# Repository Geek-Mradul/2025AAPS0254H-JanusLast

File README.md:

# 🚀 Team JANUS Avionics - Round 3 PCB Design

This repository contains the PCB design solution for the final round of the Team JANUS Avionics Subsystem inductions for 2025-2026. The project involves creating a PCB layout from a provided schematic using KiCad.

---

## 📋 Task Requirements

The goal was to design a functional PCB based on a given schematic. The board includes an STM32 MCU, a BMP280 sensor, a USB-to-UART bridge, and a Micro-USB port for power and data.

The design adheres to the following key constraints as specified in the problem statement:
* **Component Footprints**: The problem statement allowed for modifying component footprints as required. For this design, standard footprints were used.
* **Trace Widths**: Separate trace widths are used for power and signal lines to ensure stable power delivery.
* **Ground Plane**: The bottom copper layer is dedicated to a solid ground plane for signal integrity and noise reduction.
* **Vias**: Vias are used as needed to route signals between the top and bottom layers.
* **Manual Routing**: All routing was performed manually; auto-routing was strictly prohibited.

---

## 📁 Repository Contents

* `NewFile.kicad_pro`: The main KiCad project file.
* `NewFile.kicad_sch`: The schematic file containing the complete circuit diagram.
* `NewFile.kicad_pcb`: The final PCB layout file.
* `README.md`: This file.

---

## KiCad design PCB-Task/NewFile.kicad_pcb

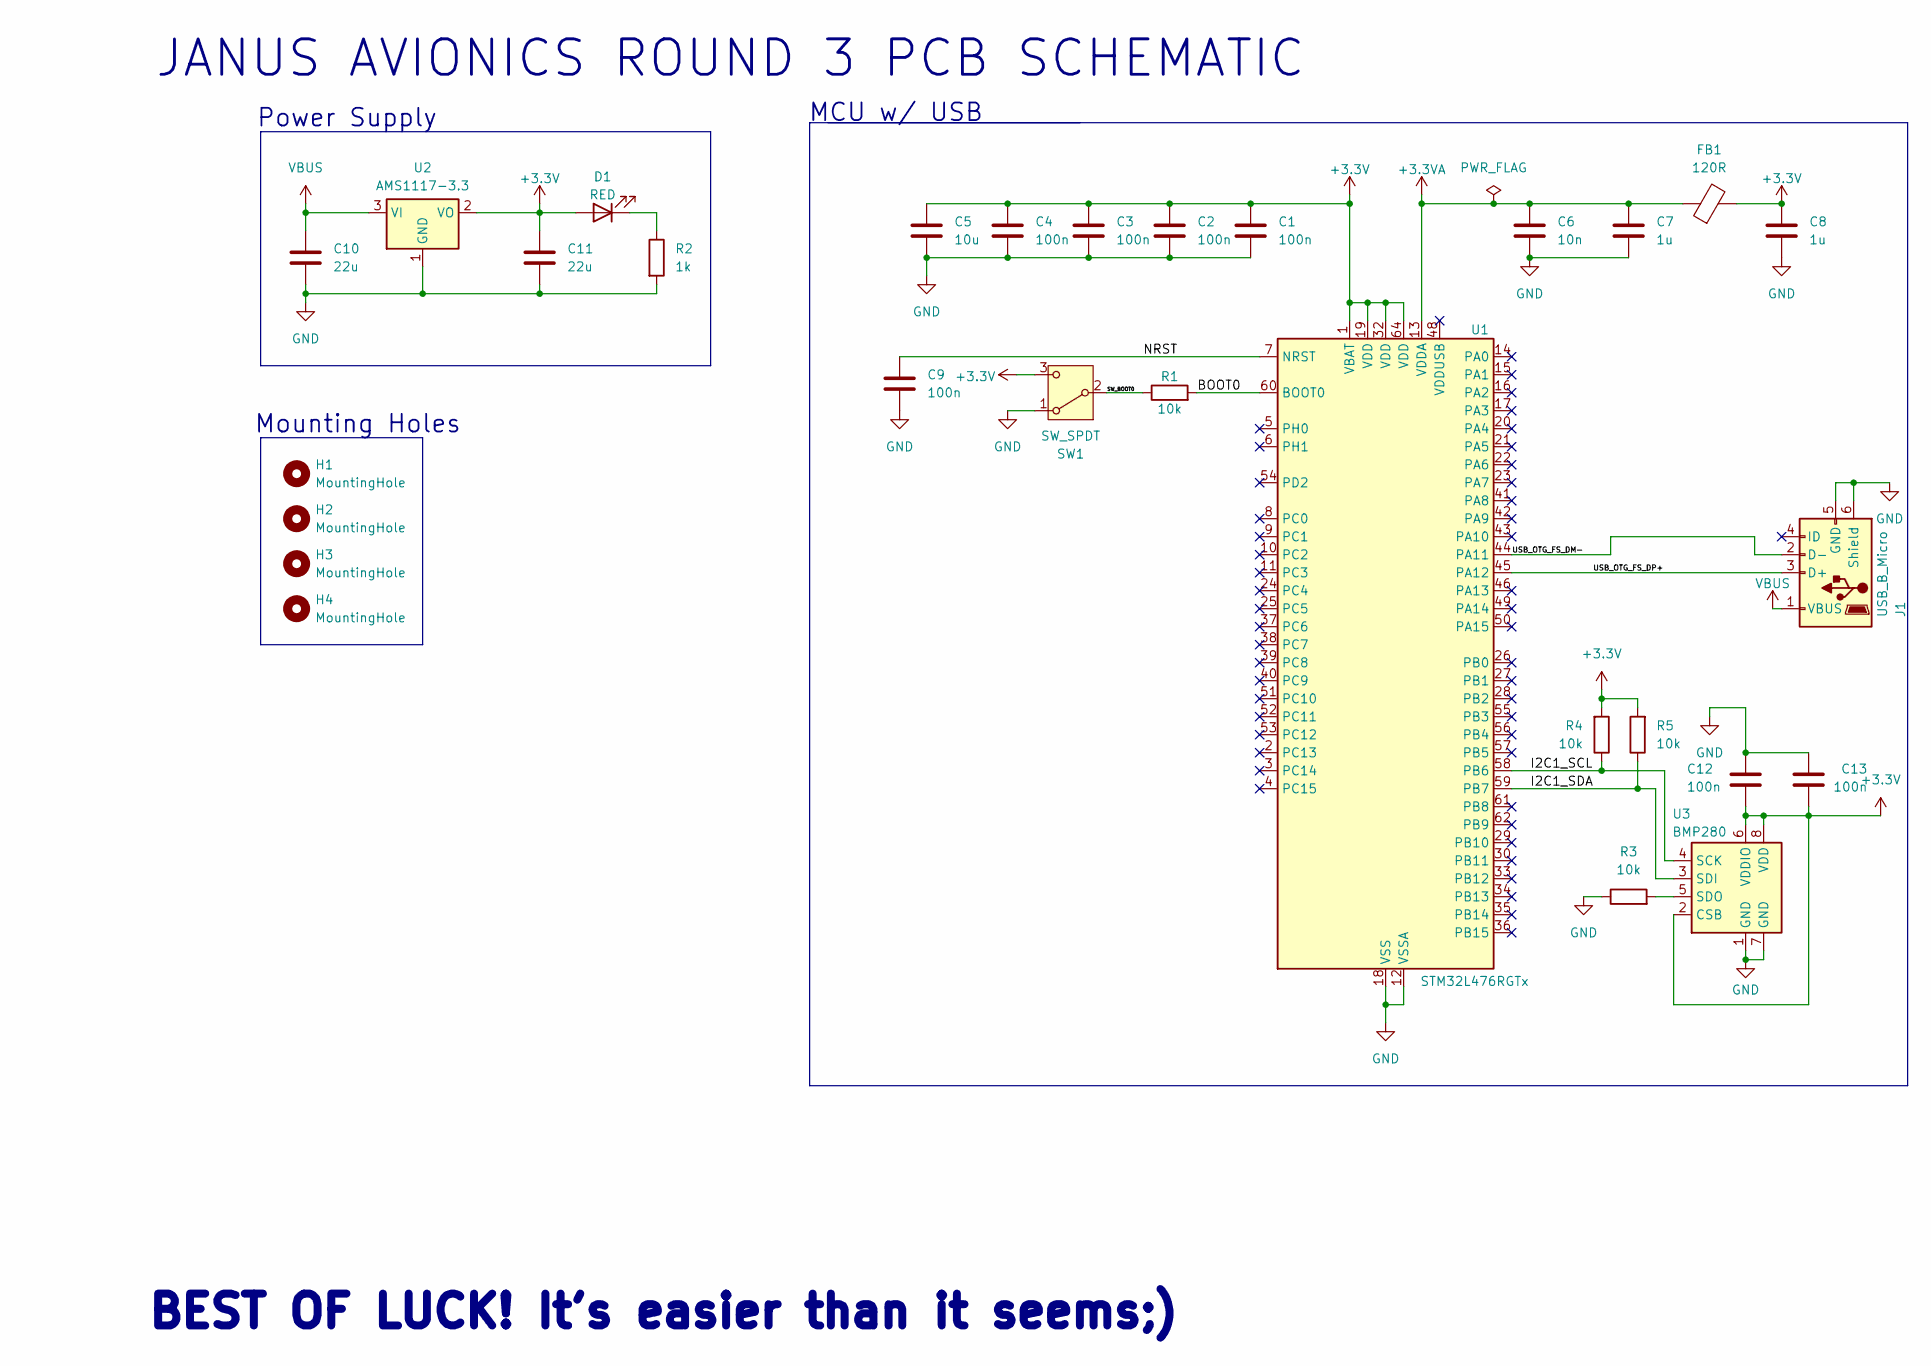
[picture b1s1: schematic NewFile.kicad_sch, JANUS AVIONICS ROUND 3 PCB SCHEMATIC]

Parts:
C1, C2, C3, C4, C9, C12, C13: 100n; C_0402_1005Metric
C5: 10u; C_0603_1608Metric
C6: 10n; C_0402_1005Metric
C7, C8: 1u; C_0402_1005Metric
C10, C11: 22u; C_0805_2012Metric
D1: RED; LED_0603_1608Metric
FB1: 120R; L_0603_1608Metric
H1, H2, H3, H4: MountingHole; MountingHole_2.2mm_M2
J1: USB_B_Micro; USB_Micro-B_Wuerth_629105150521
R1, R3, R4, R5: 10k; R_0402_1005Metric
R2: 1k; R_0402_1005Metric
SW1: SW_SPDT; SW_SPDT_PCM12
U1: STM32L476RGTx; LQFP-64_10x10mm_P0.5mm
U2: AMS1117-3.3; SOT-223-3_TabPin2
U3: BMP280; Bosch_LGA-8_2x2.5mm_P0.65mm_ClockwisePinNumbering

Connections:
+3.3V: C1.1, C2.1, C3.1, C4.1, C5.1, C8.1, C11.1, C12.2, C13.2, D1.2 (A), FB1.2, R4.2, R5.2, SW1.3 (C), U1.1 (VBAT), U1.19 (VDD), U1.32 (VDD), U1.64 (VDD), U2.2 (VO), U3.2 (CSB), U3.6 (VDDIO), U3.8 (VDD)
+3.3VA: C6.1, C7.1, FB1.1, U1.13 (VDDA)
/BOOT0: R1.2, U1.60 (BOOT0)
/I2C1_SCL: R4.1, U1.58 (PB6), U3.4 (SCK)
/I2C1_SDA: R5.1, U1.59 (PB7), U3.3 (SDI)
/NRST: C9.1, U1.7 (NRST)
/SW_BOOT0: R1.1, SW1.2 (B)
/USB_OTG_FS_DM-: J1.2 (D-), U1.44 (PA11)
/USB_OTG_FS_DP+: J1.3 (D+), U1.45 (PA12)
GND: C1.2, C2.2, C3.2, C4.2, C5.2, C6.2, C7.2, C8.2, C9.2, C10.2, C11.2, C12.1, C13.1, J1.5 (GND), J1.6 (Shield), R2.2, R3.1, SW1.1 (A), U1.12 (VSSA), U1.18 (VSS), U1.31 (VSS), U1.47 (VSS), U1.63 (VSS), U2.1 (GND), U3.1 (GND), U3.7 (GND)
unnamed: D1.1 (K), R2.1
unnamed: R3.2, U3.5 (SDO)
VBUS: C10.1, J1.1 (VBUS), U2.3 (VI)

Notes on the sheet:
MCU w/ USB
Mounting Holes
JANUS AVIONICS ROUND 3 PCB SCHEMATIC
Power Supply
BEST OF LUCK! It's easier than it seems;)

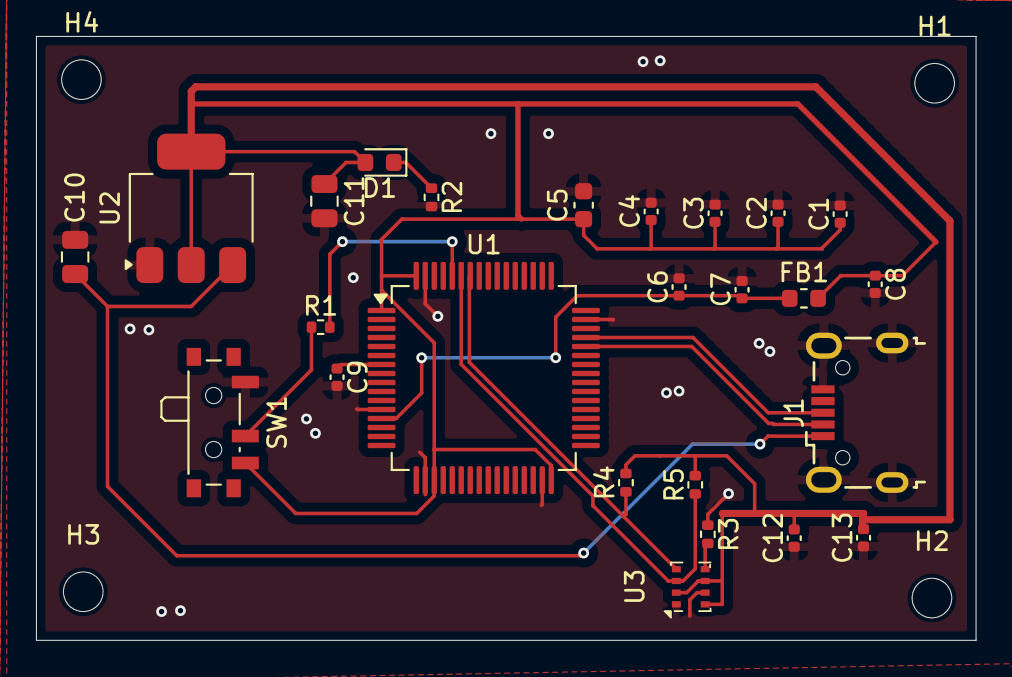
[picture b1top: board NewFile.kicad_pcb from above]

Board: 2 copper layers, 52.2 x 33.6 mm, 29 parts (0 on the bottom side), 13 nets.
